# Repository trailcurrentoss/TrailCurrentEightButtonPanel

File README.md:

# TrailCurrent Tapper

Eight-button control panel that sends toggle commands over a CAN bus interface with OTA firmware update capability. Supports targeting Torrent (PWM lighting) or Switchback (relay) modules via build-time configuration. Part of the [TrailCurrent](https://trailcurrent.com) open-source vehicle platform.

## Hardware Overview

- **Microcontroller:** ESP32 (WROOM32)
- **Function:** Physical button panel for CAN bus device control
- **Key Features:**
  - 8 momentary buttons with LED backlights
  - Button press: toggle device on/off
  - Build-time target device selection (Torrent or Switchback, instance 0-2)
  - CAN bus communication at 500 kbps
  - Over-the-air (OTA) firmware updates via WiFi
  - mDNS-based network discovery
  - LED state feedback from CAN bus
  - FreeCAD enclosure design

## Hardware Requirements

### Components

- **Microcontroller:** ESP32 development board
- **CAN Transceiver:** Vehicle CAN bus interface (TX: GPIO 15, RX: GPIO 13)

### Pin Connections

**Buttons (INPUT_PULLUP):**

| GPIO | Function |
|------|----------|
| 34 | Button 1 |
| 25 | Button 2 |
| 27 | Button 3 |
| 12 | Button 4 |
| 16 | Button 5 |
| 22 | Button 6 |
| 21 | Button 7 |
| 18 | Button 8 |

**LED Backlights (OUTPUT):**

| GPIO | Function |
|------|----------|
| 32 | LED 1 |
| 33 | LED 2 |
| 26 | LED 3 |
| 14 | LED 4 |
| 4 | LED 5 |
| 23 | LED 6 |
| 19 | LED 7 |
| 17 | LED 8 |

### KiCAD Library Dependencies

This project uses the consolidated [TrailCurrentKiCADLibraries](https://github.com/trailcurrentoss/TrailCurrentKiCADLibraries).

**Setup:**

```bash
# Clone the library
git clone git@github.com:trailcurrentoss/TrailCurrentKiCADLibraries.git

# Set environment variables (add to ~/.bashrc or ~/.zshrc)
export TRAILCURRENT_SYMBOL_DIR="/path/to/TrailCurrentKiCADLibraries/symbols"
export TRAILCURRENT_FOOTPRINT_DIR="/path/to/TrailCurrentKiCADLibraries/footprints"
export TRAILCURRENT_3DMODEL_DIR="/path/to/TrailCurrentKiCADLibraries/3d_models"
```

See [KICAD_ENVIRONMENT_SETUP.md](https://github.com/trailcurrentoss/TrailCurrentKiCADLibraries/blob/main/KICAD_ENVIRONMENT_SETUP.md) in the library repository for detailed setup instructions.

## Opening the Project

1. **Set up environment variables** (see Library Dependencies above)
2. **Open KiCAD:**
   ```bash
   kicad EDA/trailcurrent-tapper.kicad_pro
   ```
3. **Verify libraries load** - All symbol and footprint libraries should resolve without errors
4. **View 3D models** - Open PCB and press `Alt+3` to view the 3D visualization

## Firmware

ESP-IDF based firmware in the `main/` directory.

**Prerequisites:**
- [ESP-IDF](https://docs.espressif.com/projects/esp-idf/en/stable/esp32/get-started/) v4.1 or later

**Build and flash:**
```bash
# Set up ESP-IDF environment
. $IDF_PATH/export.sh

# Build for Torrent instance 0 (default)
idf.py build

# Build for a specific target device and instance
idf.py build -DTARGET_DEVICE=switchback -DDEVICE_INSTANCE=2

# Flash via serial
idf.py -p /dev/ttyUSB0 flash monitor

# OTA update — always use the app-only binary, never the merged binary
curl -X POST http://esp32-XXYYZZ.local/ota --data-binary @build/tapper_torrent_addr0.bin
```

### Target Device Configuration

Each Tapper is built to target a specific device type and instance, set at compile time via CMake flags:

| Flag | Values | Default | Description |
|------|--------|---------|-------------|
| `TARGET_DEVICE` | `torrent`, `switchback` | `torrent` | Target device type |
| `DEVICE_INSTANCE` | `0`, `1`, `2` | `0` | Target device instance |

These flags determine the CAN IDs used for toggle commands and status feedback:

**Torrent (PWM lighting controller):**

| Instance | Toggle TX | Status RX | Status Format |
|----------|-----------|-----------|---------------|
| 0 | 0x18 | 0x1B | 8 bytes (one per channel, 0-255) |
| 1 | 0x19 | 0x1C | 8 bytes |
| 2 | 0x1A | 0x1D | 8 bytes |

**Switchback (relay module):**

| Instance | Toggle TX | Status RX | Status Format |
|----------|-----------|-----------|---------------|
| 0 | 0x25 | 0x28 | 1 byte (bitmask, one bit per relay) |
| 1 | 0x26 | 0x29 | 1 byte |
| 2 | 0x27 | 0x2A | 1 byte |

When switching between device types, run `idf.py fullclean` before rebuilding to clear cached CMake variables.

Multiple Tappers can target the same device instance — there is no limit.

#### Building All Variants

Use `build-all.sh` to build all 6 firmware variants (2 targets x 3 addresses):

```bash
./build-all.sh
```

This produces two binaries per variant — one for OTA updates, one for the web flasher:

| File | Contents | Used By |
|------|----------|---------|
| `build/tapper_{target}_addr{N}.bin` | Application image only | Headwaters OTA (`deploy.sh`, `ota.js`), direct `curl` uploads |
| `build/tapper_{target}_addr{N}_merged.bin` | Bootloader + partition table + OTA data + application | Web flasher (full flash at 0x0) |

The two binary types exist because OTA and the web flasher write to different targets. Headwaters OTA sends the binary to the device's `/ota` HTTP endpoint, which calls `esp_ota_write` to write it to a single app partition. That function validates the image as an application — a merged binary starts with the bootloader instead of an app header, so it would fail validation. The web flasher writes the entire flash contents starting at offset 0x0, so it needs all partitions combined into one file.

#### Creating a GitHub Release

After building all variants, attach all 12 binaries (6 app-only + 6 merged) as release assets:

```bash
git tag -a v1.0.0 -m "Firmware release v1.0.0"
git push origin v1.0.0

gh release create v1.0.0 \
  build/tapper_torrent_addr0.bin \
  build/tapper_torrent_addr1.bin \
  build/tapper_torrent_addr2.bin \
  build/tapper_switchback_addr0.bin \
  build/tapper_switchback_addr1.bin \
  build/tapper_switchback_addr2.bin \
  build/tapper_torrent_addr0_merged.bin \
  build/tapper_torrent_addr1_merged.bin \
  build/tapper_torrent_addr2_merged.bin \
  build/tapper_switchback_addr0_merged.bin \
  build/tapper_switchback_addr1_merged.bin \
  build/tapper_switchback_addr2_merged.bin \
  --repo trailcurrentoss/TrailCurrentTapper \
  --title "v1.0.0" \
  --notes "Firmware release v1.0.0"
```

Both the Headwaters deployment system and the web flasher pull from GitHub releases. The web flasher matches `_merged.bin` files by name for full-flash use. The Headwaters deployment system (`fetch-firmware.sh`) downloads the app-only `tapper_{target}_addr{N}.bin` files for OTA delivery.

### CAN Bus Protocol

**Transmit (Panel to Bus):**

| CAN ID | Bytes | Description |
|--------|-------|-------------|
| Torrent: 0x18-0x1A | 1 | Button toggle (byte 0 = button index 0-7) |
| Switchback: 0x25-0x27 | 1 | Button toggle (byte 0 = button index 0-7) |

**Receive (Bus to Panel):**

| CAN ID | Bytes | Description |
|--------|-------|-------------|
| 0x00 | 3 | OTA update trigger (MAC-based device targeting) |
| 0x01 | var | WiFi credential provisioning (chunked protocol) |
| 0x02 | 0 | Discovery trigger (broadcast) |
| 0x04 | 6 | Version report on boot: `[mac3, mac4, mac5, major, minor, patch]` |
| Torrent: 0x1B-0x1D | 8 | LED state (1 byte per channel, 0=off, non-zero=on) |
| Switchback: 0x28-0x2A | 1 | LED state (bitmask, 1 bit per relay) |

### Button Behavior

- **Press**: Sends toggle command (debounced, 50ms). Byte 0 = button index (0-7).

### OTA Updates

WiFi credentials are provisioned over CAN (ID 0x01) and stored in NVS. When an OTA trigger (ID 0x00) matches this device's MAC-derived hostname, the module connects to WiFi, advertises via mDNS, and accepts firmware uploads at `POST /ota`.

### Network Discovery

On CAN trigger (ID 0x02), the module joins WiFi and advertises itself via mDNS service `_trailcurrent._tcp` with TXT records for module type, target device, CAN ID, device instance, and firmware version.

## Manufacturing

- **PCB Files:** Ready for fabrication via standard PCB services (JLCPCB, OSH Park, etc.)
- **BOM Generation:** Export BOM from KiCAD schematic (Tools > Generate BOM)
- **Enclosure:** FreeCAD design included in `CAD/` directory
- **JLCPCB Assembly:** See [BOM_ASSEMBLY_WORKFLOW.md](https://github.com/trailcurrentoss/TrailCurrentKiCADLibraries/blob/main/BOM_ASSEMBLY_WORKFLOW.md) for detailed assembly workflow

## Project Structure

```
├── CAD/                          # FreeCAD enclosure design
├── EDA/                          # KiCAD hardware design files
│   ├── trailcurrent-tapper.kicad_pro
│   ├── trailcurrent-tapper.kicad_sch
│   └── trailcurrent-tapper.kicad_pcb
├── main/                         # ESP-IDF firmware source
│   ├── main.c                    # Button handling, LED control, CAN communication
│   ├── ota.c / ota.h             # OTA updates and WiFi provisioning
│   ├── discovery.c / discovery.h # mDNS network discovery
│   ├── CMakeLists.txt            # Component build configuration
│   └── idf_component.yml         # Managed component dependencies
├── CMakeLists.txt                # ESP-IDF project root
├── sdkconfig.defaults            # Default SDK configuration
├── build-all.sh                  # Build all 6 variants (2 targets x 3 addresses)
└── partitions.csv                # ESP32 flash partition layout (dual OTA)
```

## License

MIT License - See LICENSE file for details.

## Contributing

Improvements and contributions are welcome! Please submit issues or pull requests.

## Support

For questions about:
- **KiCAD setup:** See [KICAD_ENVIRONMENT_SETUP.md](https://github.com/trailcurrentoss/TrailCurrentKiCADLibraries/blob/main/KICAD_ENVIRONMENT_SETUP.md)
- **Assembly workflow:** See [BOM_ASSEMBLY_WORKFLOW.md](https://github.com/trailcurrentoss/TrailCurrentKiCADLibraries/blob/main/BOM_ASSEMBLY_WORKFLOW.md)

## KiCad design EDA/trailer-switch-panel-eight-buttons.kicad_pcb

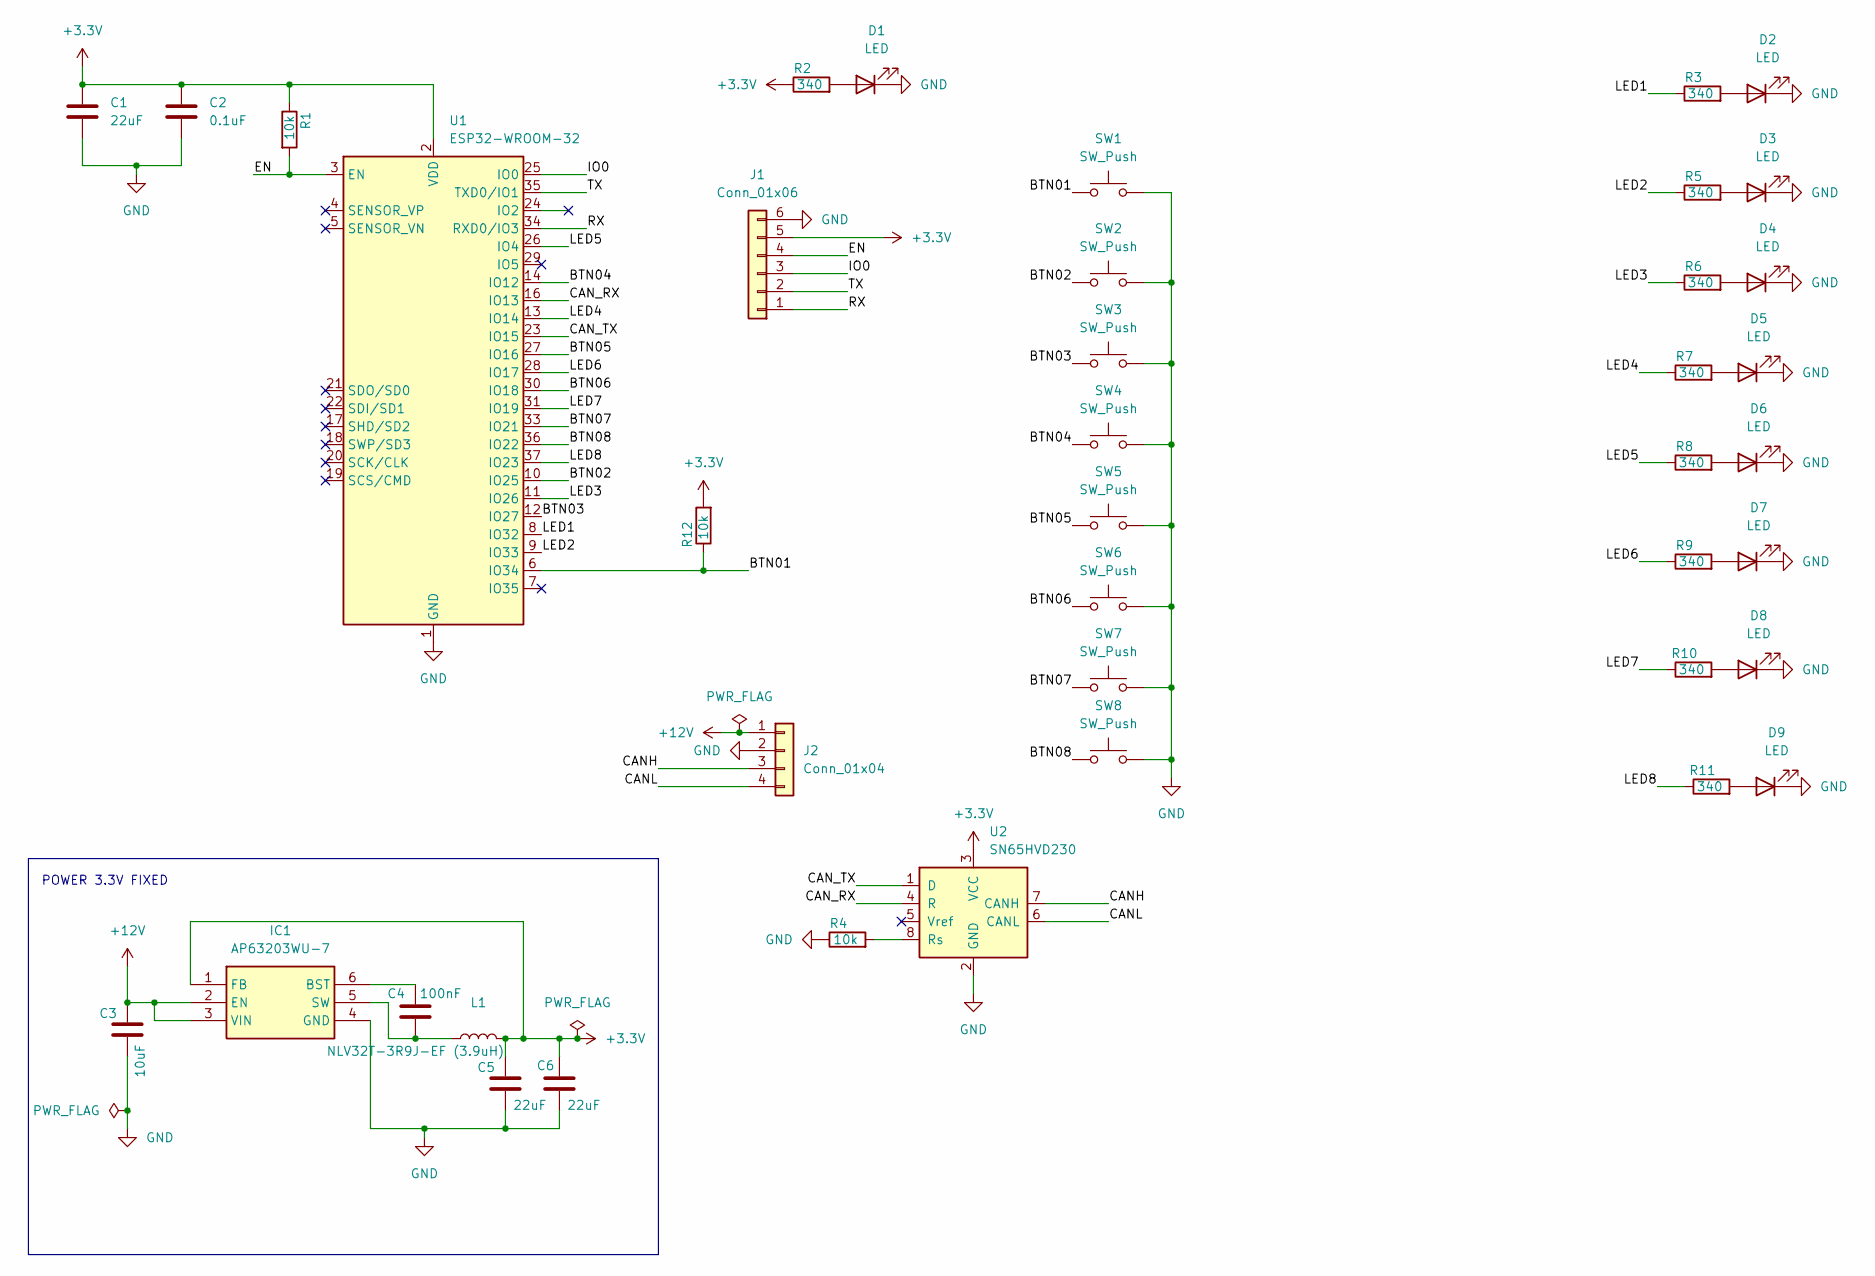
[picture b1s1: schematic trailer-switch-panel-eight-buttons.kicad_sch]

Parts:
C1, C5, C6: 22uF; C_1206_3216Metric_Pad1.33x1.80mm_HandSolder
C2: 0.1uF; C_1206_3216Metric_Pad1.33x1.80mm_HandSolder
C3: 10uF; C_1206_3216Metric
C4: 100nF; C_1206_3216Metric
D1, D2, D3, D4, D5, D6, D7, D8, D9: LED; LED_1206_3216Metric_Pad1.42x1.75mm_HandSolder
IC1: AP63203WU-7; AP63203WU7; Mouser Part Number 621-AP63203WU-7
J1: Conn_01x06; PinHeader_1x06_P2.54mm_Horizontal
J2: Conn_01x04; CAN_PLUS_POWER
L1: NLV32T-3R9J-EF (3.9uH); INDM3225X240N
R1, R4, R12: 10k; R_1206_3216Metric_Pad1.30x1.75mm_HandSolder
R2, R3, R5, R6, R7, R8, R9, R10, R11: 340; R_1206_3216Metric_Pad1.30x1.75mm_HandSolder
SW1, SW2, SW3, SW4, SW5, SW6, SW7, SW8: SW_Push; SW_PUSH_6mm
U1: ESP32-WROOM-32; ESP32-WROOM-32U
U2: SN65HVD230; SOIC-8_3.9x4.9mm_P1.27mm

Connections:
+3.3V: C1.1, C2.1, C5.1, C6.1, IC1.1 (FB), J1.5, L1.2, R1.1, R2.1, R12.2, U1.2 (VDD), U2.3 (VCC)
+12V: C3.1, IC1.2 (EN), IC1.3 (VIN), J2.1
/BTN01: R12.1, SW1.1, U1.6 (IO34)
/BTN02: SW2.1, U1.10 (IO25)
/BTN03: SW3.1, U1.12 (IO27)
/BTN04: SW4.1, U1.14 (IO12)
/BTN05: SW5.1, U1.27 (IO16)
/BTN06: SW6.1, U1.30 (IO18)
/BTN07: SW7.1, U1.33 (IO21)
/BTN08: SW8.1, U1.36 (IO22)
/CANH: J2.3, U2.7 (CANH)
/CANL: J2.4, U2.6 (CANL)
/CAN_RX: U1.16 (IO13), U2.4 (R)
/CAN_TX: U1.23 (IO15), U2.1 (D)
/EN: J1.4, R1.2, U1.3 (EN)
/IO0: J1.3, U1.25 (IO0)
/LED1: R3.1, U1.8 (IO32)
/LED2: R5.1, U1.9 (IO33)
/LED3: R6.1, U1.11 (IO26)
/LED4: R7.1, U1.13 (IO14)
/LED5: R8.1, U1.26 (IO4)
/LED6: R9.1, U1.28 (IO17)
/LED7: R10.1, U1.31 (IO19)
/LED8: R11.1, U1.37 (IO23)
/RX: J1.1, U1.34 (RXD0/IO3)
/TX: J1.2, U1.35 (TXD0/IO1)
GND: C1.2, C2.2, C3.2, C5.2, C6.2, D1.1 (K), D2.1 (K), D3.1 (K), D4.1 (K), D5.1 (K), D6.1 (K), D7.1 (K), D8.1 (K), D9.1 (K), IC1.4 (GND), J1.6, J2.2, R4.1, SW1.2, SW2.2, SW3.2, SW4.2, SW5.2, SW6.2, SW7.2, SW8.2, U1.1 (GND), U1.15 (GND), U1.38 (GND), U1.39 (GND), U2.2 (GND)
unnamed: D1.2 (A), R2.2
unnamed: D2.2 (A), R3.2
unnamed: D3.2 (A), R5.2
unnamed: D4.2 (A), R6.2
unnamed: D5.2 (A), R7.2
unnamed: D6.2 (A), R8.2
unnamed: D7.2 (A), R9.2
unnamed: D8.2 (A), R10.2
unnamed: D9.2 (A), R11.2
unnamed: C4.1, IC1.6 (BST)
unnamed: C4.2, IC1.5 (SW), L1.1
unnamed: R4.2, U2.8 (Rs)

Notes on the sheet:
POWER 3.3V FIXED

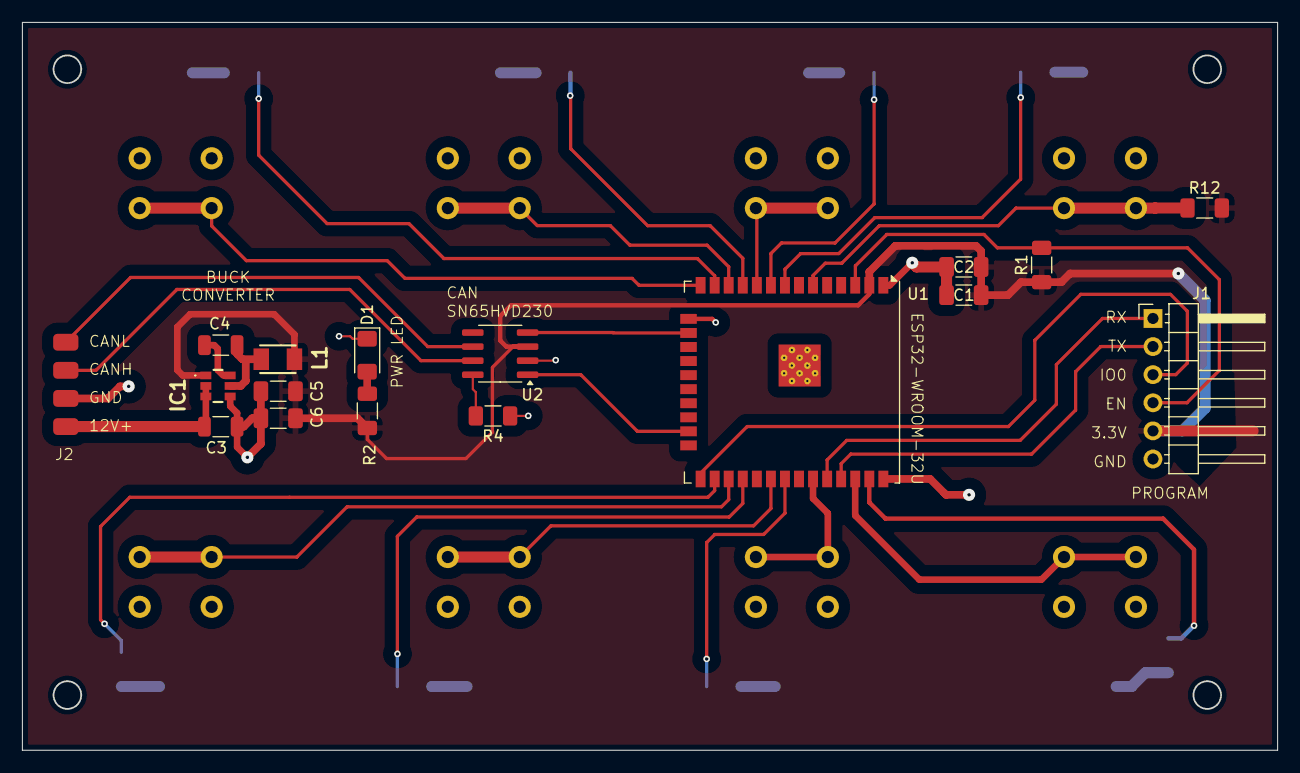
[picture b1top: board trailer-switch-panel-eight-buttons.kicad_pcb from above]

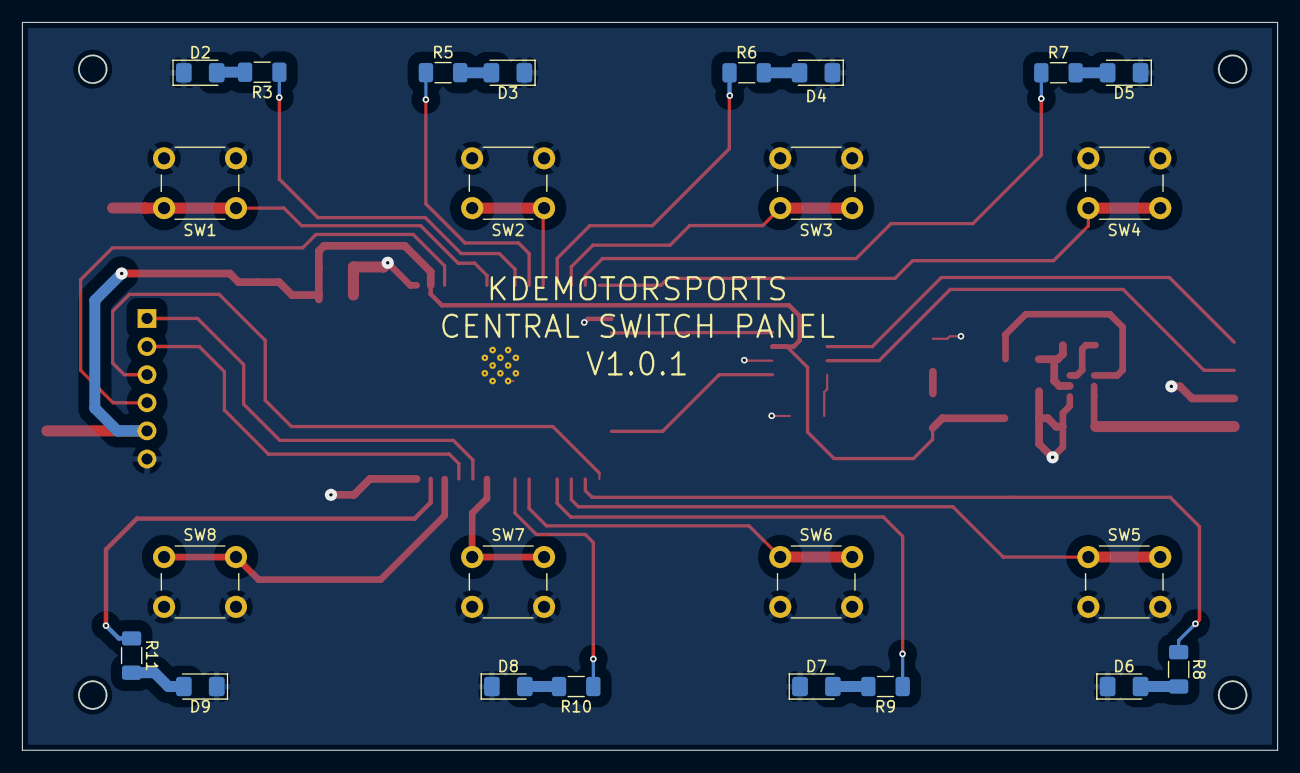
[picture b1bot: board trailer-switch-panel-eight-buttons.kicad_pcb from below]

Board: 2 copper layers, 113.3 x 65.7 mm, 41 parts (24 on the bottom side), 39 nets.

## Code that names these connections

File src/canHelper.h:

#pragma once
#include "globals.h"
#include "driver/twai.h"
#define CAN_RX 13
#define CAN_TX 15
#define POLLING_RATE_MS 33
#define CAN_SEND_MESSAGE_IDENTIFIER 0x18;
static bool driver_installed = false;

namespace canHelper
{
  void canSetup()
  {
    twai_general_config_t g_config = TWAI_GENERAL_CONFIG_DEFAULT((gpio_num_t)CAN_TX, (gpio_num_t)CAN_RX, TWAI_MODE_NO_ACK);
    twai_timing_config_t t_config = TWAI_TIMING_CONFIG_500KBITS(); // Look in the api-reference for other speed sets.
    twai_filter_config_t f_config = {
        .acceptance_code = (0x1B << 21),
        .acceptance_mask = 0x1FFFFFFF,
        .single_filter = true};
    // Install TWAI driver
    if (twai_driver_install(&g_config, &t_config, &f_config) == ESP_OK)
    {
      debugln("Driver installed");
    }
    else
    {
      debugln("Failed to install driver");
      return;
    }

    // Start TWAI driver
    if (twai_start() == ESP_OK)
    {
      debugln("Driver started");
    }
    else
    {
      debugln("Failed to start driver");
      return;
    }

    // Reconfigure alerts to detect frame receive, Bus-Off error and RX queue full states
    uint32_t alerts_to_enable = TWAI_ALERT_RX_DATA | TWAI_ALERT_ERR_PASS | TWAI_ALERT_BUS_ERROR | TWAI_ALERT_RX_QUEUE_FULL;
    if (twai_reconfigure_alerts(alerts_to_enable, NULL) == ESP_OK)
    {
      debugln("CAN Alerts reconfigured");
    }
    else
    {
      debugln("Failed to reconfigure alerts");
      return;
    }

    // TWAI driver is now successfully installed and started
    driver_installed = true;
  }

  static void send_message(int btn)
  {
    // Send message
    int aryLightValues[8] = {0, 0, 0, 0, 0, 0, 0, 0};
    aryLightValues[btn - 1] = 255;
    // Configure message to transmit
    twai_message_t message;
    message.identifier = CAN_SEND_MESSAGE_IDENTIFIER;
    message.extd = false; // Using CAN 2.0 extended id allowing up to 536870911 identifiers
    message.rtr = false;
    message.data_length_code = 1;
    message.data[0] = (btn - 1);

    // Queue message for transmission
    if (twai_transmit(&message, pdMS_TO_TICKS(10)) == ESP_OK)
    {
      debugln("Message queued for transmission");
    }
    else
    {
      debugln("Failed to queue message for transmission");
    }
  }

  static void handle_rx_message(twai_message_t &message)
  {
    // Process received message
    if (message.extd)
    {
      debugln("Message is in Extended Format");
    }
    else
    {
      debugln("Message is in Standard Format");
    }
    debugf("ID: %lx\nByte:", message.identifier);
    if (message.identifier == 27)
    {
      if (!(message.rtr))
      {
        if (message.data[0] == 00)
        {
          digitalWrite(LED1_PIN, LOW);
        }
        else
        {
          digitalWrite(LED1_PIN, HIGH);
        }

        if (message.data[1] == 00)
        {
          digitalWrite(LED2_PIN, LOW);
        }
        else
        {
          digitalWrite(LED2_PIN, HIGH);
        }

        if (message.data[2] == 00)
        {
          digitalWrite(LED3_PIN, LOW);
        }
        else
        {
          digitalWrite(LED3_PIN, HIGH);
        }

        if (message.data[3] == 00)
        {
          digitalWrite(LED4_PIN, LOW);
        }
        else
        {
          digitalWrite(LED4_PIN, HIGH);
        }

        if (message.data[4] == 00)
        {
          digitalWrite(LED5_PIN, LOW);
        }
        else
        {
          digitalWrite(LED5_PIN, HIGH);
        }

        if (message.data[5] == 00)
        {
          digitalWrite(LED6_PIN, LOW);
        }
        else
        {
          digitalWrite(LED6_PIN, HIGH);
        }

        if (message.data[6] == 00)
        {
          digitalWrite(LED7_PIN, LOW);
        }
        else
        {
          digitalWrite(LED7_PIN, HIGH);
        }

        if (message.data[7] == 00)
        {
          digitalWrite(LED8_PIN, LOW);
        }
        else
        {
          digitalWrite(LED8_PIN, HIGH);
        }

        for (int i = 0; i < message.data_length_code; i++)
        {
          debugg(" %d = %02x,", i, message.data[i]);
        }
        debugln("");
      }
    }
  }

  void canLoop()
  {
    if (!driver_installed)
    {
      // Driver not installed
      delay(1000);
      return;
    }
    // Check if alert happened
    uint32_t alerts_triggered;
    twai_read_alerts(&alerts_triggered, pdMS_TO_TICKS(POLLING_RATE_MS));
    twai_status_info_t twaistatus;
    twai_get_status_info(&twaistatus);

    // Handle alerts
    if (alerts_triggered & TWAI_ALERT_ERR_PASS)
    {
      debugln("Alert: TWAI controller has become error passive.");
    }
    if (alerts_triggered & TWAI_ALERT_BUS_ERROR)
    {
      debugln("Alert: A (Bit, Stuff, CRC, Form, ACK) error has occurred on the bus.");
      debugf("Bus error count: %lu\n", twaistatus.bus_error_count);
    }
    if (alerts_triggered & TWAI_ALERT_RX_QUEUE_FULL)
    {
      debugln("Alert: The RX queue is full causing a received frame to be lost.");
      debugf("RX buffered: %lu\t", twaistatus.msgs_to_rx);
      debugf("RX missed: %lu\t", twaistatus.rx_missed_count);
      debugf("RX overrun %lu\n", twaistatus.rx_overrun_count);
    }

    // Check if message is received
    if (alerts_triggered & TWAI_ALERT_RX_DATA)
    {
      // One or more messages received. Handle all.
      twai_message_t message;
      while (twai_receive(&message, 0) == ESP_OK)
      {
        handle_rx_message(message);
      }
    }
  }
}

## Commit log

2026-02-14 Starting project
2026-02-14 Update docs: replace Codeberg URLs with GitHub references
2026-02-16 Removed Secrets.h reference. Still needs testing
2026-02-21 Jingle bells light sequence added for visual verification of OTA update
2026-02-21 Fixed old docs
2026-02-21 Test was successful removing the jingle bells lighting sequence
2026-03-15 Fixing to NO_ACK so modules can come onto and leave the can bus without disruption
2026-03-19 Added image of assembled case to readme
2026-03-27 Moved to ESP-IDF and adjusted brightness scaling.
2026-03-28 Fixed bug where discovery would disrupt CAN messaging
2026-03-28 Removing brightness in prep for tapper being able to flash to different IDs and also to control switchback
2026-03-28 Updated to allow tapper to be configured to different Torrent devices
2026-03-28 Add build flags to allow pairing of tapper to Torrent or Switchback devices
2026-03-28 Aligned discovvery and ota
2026-03-28 Fixing issue with CAN Bus stops responding when discovery happens
2026-03-29 Changes to provide version on OTA
2026-04-08 Addding CAN ID to discovery so that headwaters knows which "tapper" it discovered
2026-04-09 Adding build script for all variations of firmware
2026-04-09 Fixed merged binaries for releasese
2026-04-10 Updated build script and readme for all binary variants needed for both OTA and web flash
2026-04-15 Moving to central CAN library
